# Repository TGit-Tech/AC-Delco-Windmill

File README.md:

# AC-Delco Alternator Windmill
An AC Delco alternator Windmill for wind power generation

Release 2017.12.10-beta ( Pictures Below )
*INCOMPLETE PROJECT - Use for experimental only*
Tested in 40mph winds found that gear slippage and destruction occurs
Need to Refactor the design for more stability
However, Project has demonstrated the ability to charge @ ~ 20mph winds
This includes self-excitement ( Actual power gained )

Current Work
*INCOMPLETE PROJECT - Use for experimental only*
Current Work still needs to be built and tested.  This is the 5-blade design
updated to handle high winds better by moving the alternator to behind the post
and creating a 5-Gear system in which the miter gears will transfer to straight
gears appropriately.  This also creates a 20:1 Ratio versus Version 2017.12.10-beta
 which created a 15:1 Ration.

## Introduction
-

## Specification
- Takes 18-mph winds to barely start charging the battery
- Which doesn't take into account the ( 4V @ 0.85A = 3.4W ) Idle waste
- Can also run ( 3.7Vdc @ 0.62A = 2.294W )

## Alternator Excitement Regulation
In order to be efficient an Arduino ( Micro-controller ) must be used to adjust the alternators excitement level on the fly.  This was accomplished by designing a custom circuit detailed in the 'AltRegulator' folder.  The folder includes the Arduino Sketch last used to control excitement as well as KiCad design files.  The board was designed with the LinkSprite T8 CNC router using trace isolation. 

- Link to [http://www.linksprite.com/wiki/index.php5?title=DIY_CNC_3_Axis_Engraver_Machine_PCB_Milling_Wood_Carving_Router_Kit_Arduino_Grbl]( CNC used. )

## Raw Materials Needed
- (1) Free 12Vdc AC-Delco Auto Alternator [ $0 ]
- (10) DIN rail, slotted, 35mm, 10mm height, 1m length, aluminum [ $36.00 ]

    [https://www.automationdirect.com/adc/Shopping/Catalog/Enclosures_-z-_Subpanels_-z-_Thermal_Management_-z-_Lighting/Enclosure_Parts_-a-_Accessories/Internal_Component_Mounting_Accessories/DIN_Rails/DN-R35SAL1)](https://www.automationdirect.com/adc/Shopping/Catalog/Enclosures_-z-_Subpanels_-z-_Thermal_Management_-z-_Lighting/Enclosure_Parts_-a-_Accessories/Internal_Component_Mounting_Accessories/DIN_Rails/DN-R35SAL1)
    
- (1) Double 5" x 144" Beige Vinyl Lap Siding [ $7.95 ]
    
    [https://www.homedepot.com/p/Double-5-in-x-144-in-Beige-Vinyl-Lap-Siding-PC50NBH/302174965](https://www.homedepot.com/p/Double-5-in-x-144-in-Beige-Vinyl-Lap-Siding-PC50NBH/302174965)

## Electrical Materials
- 14 AWG Wire; Enough for Excitement ( pole 1 ) and Regulator ( pole 2 )
- 10 AWG Wire; Alternator ( Batt. ) to Batterry
- 40 Amp Diode?
- (2) Female Solderless Connectors for Alternator ( pole 1 & pole 2 )
- (2) O-Ring Solderless Connectors for Alternator ( Batt. & Ground )
- Incomplete list; check back later

## Bolts Needed
    - (1) 5/16" x 5" Coarse Bolt    Hub-Mount Cross Bolt
    - (1) 5/16" x 2" Bolt           For Hub Center
    - (2) 5/16" Nuts                For Double Nuts on Hub Bolt
    - (1) 5/16" x ?" Bolt           For Alternator Top Mount ( Alt Threaded Hole )
    - (1) 3/8" x ?" Bolt            For Alternator Bottom Mount
    - (1) 3/8" Nut                  For Alternator Bottom Mount
    - (4) #10-24 x 2" Screws        For 4-Rail Gears ( 9.1x Step Up )
    - (8) #10 Nuts                  For Double nuts on each Gear screw
    - (8) #10 x 3/4" Wide Washers   For each side of Rail Gears
    - (9) #10-24 x 1/2" Screws      For Vinyl Siding to DIN / 3-per-blade
    - (9) #10 Standard Washers      For Vinyl Siding to DIN / 3-per-blade
    - (9) #10 Nuts                  For Vinyl Siding to DIN / 3-per-blade
    
## Tools Needed
- Wrench Sizes
    - Phillips Head Screwdriver for #10 Screws
    - 3/8" for #10 Machine Screws
    - 1/2" for Hub, Alt Top Mount
    - 9/16" for Alt Bottom Mount
    - 15/16" for Alt Center Bolt
    
- Drill Bits
    - Drill bit for Top Alternator Bolt hole size 5/16" bolt

## Knowledge obtained
- Alternator excitement
    - Pole #1 closest to Batt. is Excitement Source
    - Pole #2 Turns ON/OFF Pole #1 Excitement at ~15Vdc and under
    - Pole #2 Isn't linear ( i.e. doesn't apply more excitement as voltage goes down )
    - Pole #1 @ 2.8Vdc,  0.35A = 0.98W but isn't strong enough to build voltage
    - Pole #1 @ 4.5Vdc,  1.24A = 5.58W is IDEAL for 9x gear-up
    - Pole #1 @ 10.7Vdc, 2.60A = 27.82W
    - Pole #1 @ 14.2Vdc, 3.50A = 49.7W
- Wiring
    - Use diodes to route alternator Batt. back into Pole #1 ( excitement )
    - Use diodes to ensure Batt. feeds battery only when charge levels
    - Startup feed of 4.5Vdc diode into Pole #1
    - Using above, when wind increases excitement increases till battery can charge
    - Need a Wind kick in start ( DC-DC Buck on battery w/Arduino turn on? )
    -

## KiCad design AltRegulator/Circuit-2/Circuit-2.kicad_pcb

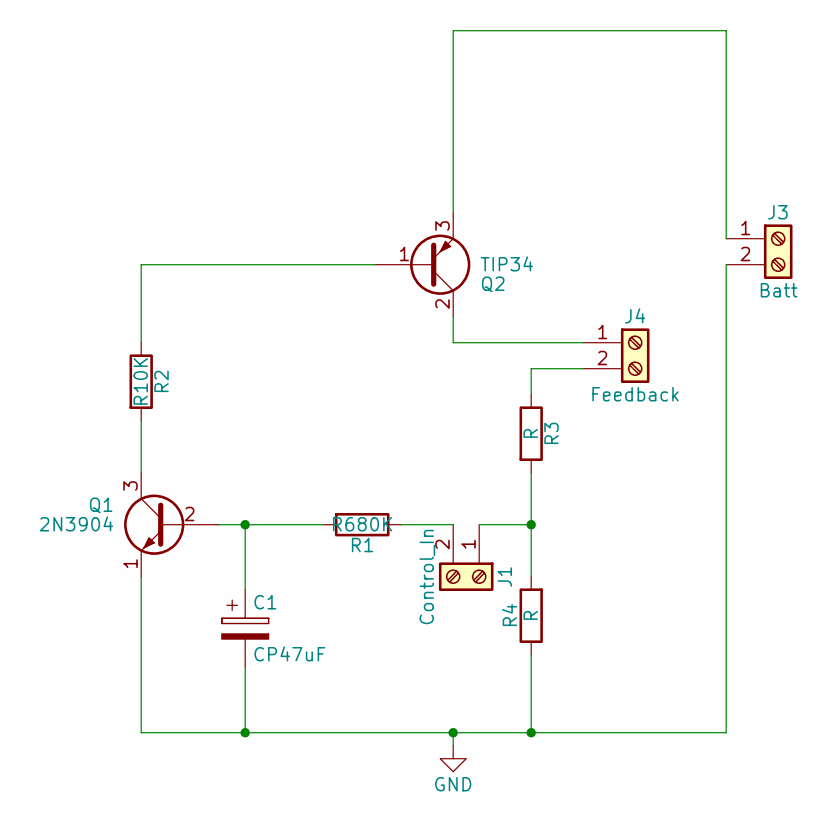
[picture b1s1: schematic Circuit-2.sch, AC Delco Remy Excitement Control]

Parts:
C1: CP47uF; CP_Radial_D5.0mm_P2.50mm
J1: Control_In; TerminalBlock_bornier-2_P5.08mm
J3: Batt; TerminalBlock_bornier-2_P5.08mm
J4: Feedback; TerminalBlock_bornier-2_P5.08mm
Q1: 2N3904; TO-92_Molded_Narrow
Q2: TIP34; TO-247_TO-3P_Vertical
R1: R680K; R_Axial_DIN0414_L11.9mm_D4.5mm_P15.24mm_Horizontal
R2: R10K; R_Axial_DIN0414_L11.9mm_D4.5mm_P15.24mm_Horizontal
R3, R4: R; R_Axial_DIN0414_L11.9mm_D4.5mm_P15.24mm_Horizontal

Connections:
GND: C1.2, J3.2, Q1.1 (E), R4.1
unnamed: C1.1, Q1.2 (B), R1.2
unnamed: J1.1, R3.2, R4.2
unnamed: J1.2, R1.1
unnamed: J3.1, Q2.3 (E)
unnamed: J4.1, Q2.2 (C)
unnamed: J4.2, R3.1
unnamed: Q1.3 (C), R2.2
unnamed: Q2.1 (B), R2.1

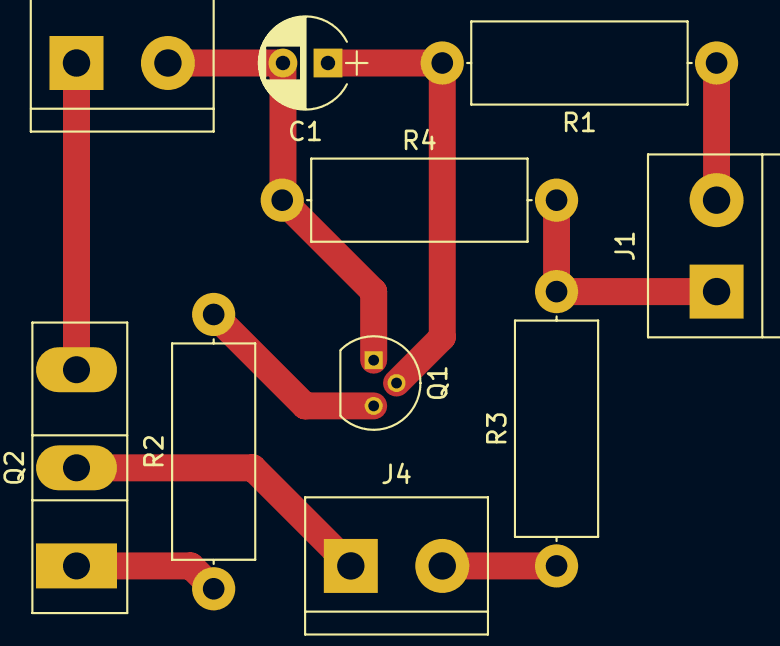
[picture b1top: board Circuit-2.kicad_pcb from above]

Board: 2 copper layers, 10 parts (0 on the bottom side), 9 nets.

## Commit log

2017-11-13 Added Pictures - Removed Gear-4 sets in wrong direction
2017-11-14 Added picture to readme.md
2017-11-17 Update to recent test.
2017-11-23 New Updates
2017-11-24 Added Alt-Fan
2017-12-10 Started Next Version 5-Blades, x20.8152 Gear Ratio. Rail Center pieces and nut holders will not fit until updated.
2017-12-11 Center pieces updated.
2018-02-13 Adding Regulator Circuit
